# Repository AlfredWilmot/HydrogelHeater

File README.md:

# Overview of temperature controller hardware

[Click to see video showing visualization of system control varialbles during use.](https://drive.google.com/file/d/1k_EgCX9lhL9ZffbRWtTjD1a9hdL3mkuH/view?usp=sharing)

# Use of temperature controller for stimuli-responsive hydrogel research

| Experimental set-up | Close-up of activated temperature-sensitive hydrogel (20x speed) driven by temperature controller|
---|---
 |

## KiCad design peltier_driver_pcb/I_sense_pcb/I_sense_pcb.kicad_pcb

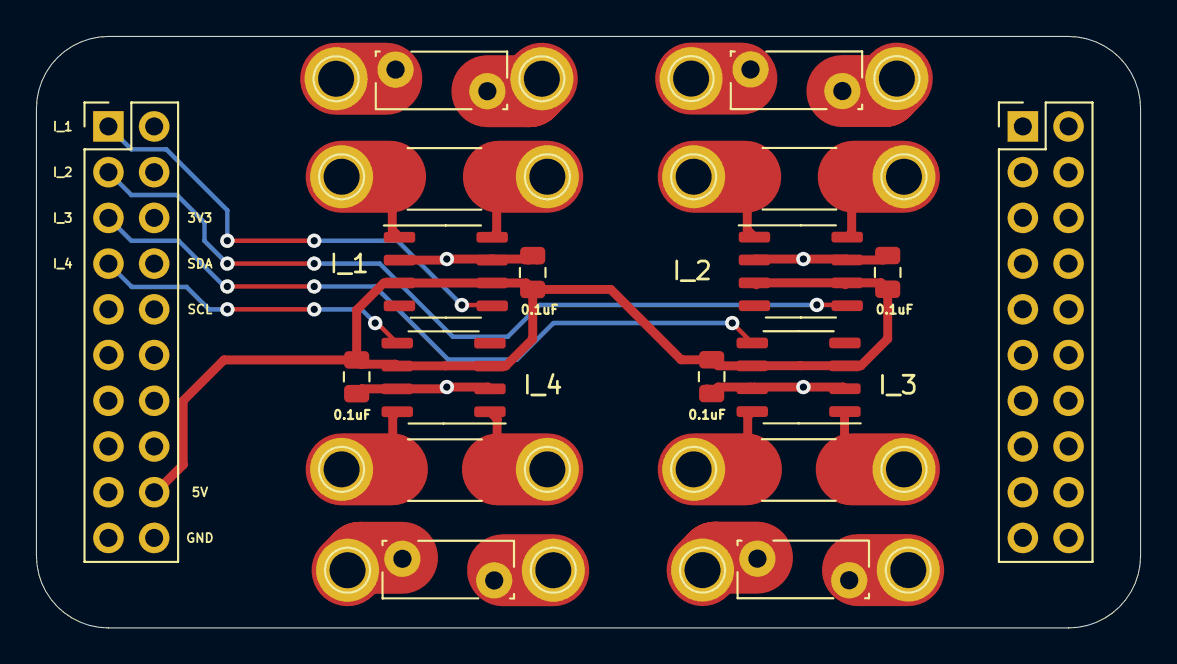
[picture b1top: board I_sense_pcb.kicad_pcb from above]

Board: 2 copper layers, 61.3 x 32.9 mm, 34 parts (0 on the bottom side), 22 nets.

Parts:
C1, C2, C3, C4: 0.1uF; C_0805_2012Metric
F1, F2, F3, F4: 3A hold, 5.1A trip; Fuse_Bourns_MF-RG300
J1, J3, J9, J11: Peltier V-; Pin_D1.0mm_L10.0mm
J2, J4, J10, J12: Driver V-; Pin_D1.0mm_L10.0mm
J5, J6, J13, J14: Peltier V+; Pin_D1.0mm_L10.0mm
J7, J8, J15, J16: Driver V+; Pin_D1.0mm_L10.0mm
J17, J18: Conn_02x10_Top_Bottom; PinHeader_2x10_P2.54mm_Vertical
R1, R2, R3, R4: 0.5m; R_2512_6332Metric
U1, U2, U3, U4: INA283; SO-8_3.9x4.9mm_P1.27mm

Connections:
+5V: C1.2, C2.2, C3.2, C4.2, J17.18, U1.3, U1.6, U2.3, U2.6, U3.3, U3.6, U4.3, U4.6
A0: J17.1, U2.5
A1: J17.3, U3.5
A2: J17.5, U4.5
A3: J17.7, U1.5
GND: C1.1, C2.1, C3.1, C4.1, J17.20, U1.2, U1.7, U2.2, U2.7, U3.2, U3.7, U4.2, U4.7
unnamed: F1.1, J2.1
unnamed: F1.2, J1.1
unnamed: F2.1, J4.1
unnamed: F2.2, J3.1
unnamed: F3.1, J10.1
unnamed: F3.2, J9.1
unnamed: F4.1, J12.1
unnamed: F4.2, J11.1
unnamed: J5.1, R1.2, U1.1
unnamed: J6.1, R2.2, U2.1
unnamed: J7.1, R1.1, U1.8
unnamed: J8.1, R2.1, U2.8
unnamed: J13.1, R3.2, U3.1
unnamed: J14.1, R4.2, U4.1
unnamed: J15.1, R3.1, U3.8
unnamed: J16.1, R4.1, U4.8

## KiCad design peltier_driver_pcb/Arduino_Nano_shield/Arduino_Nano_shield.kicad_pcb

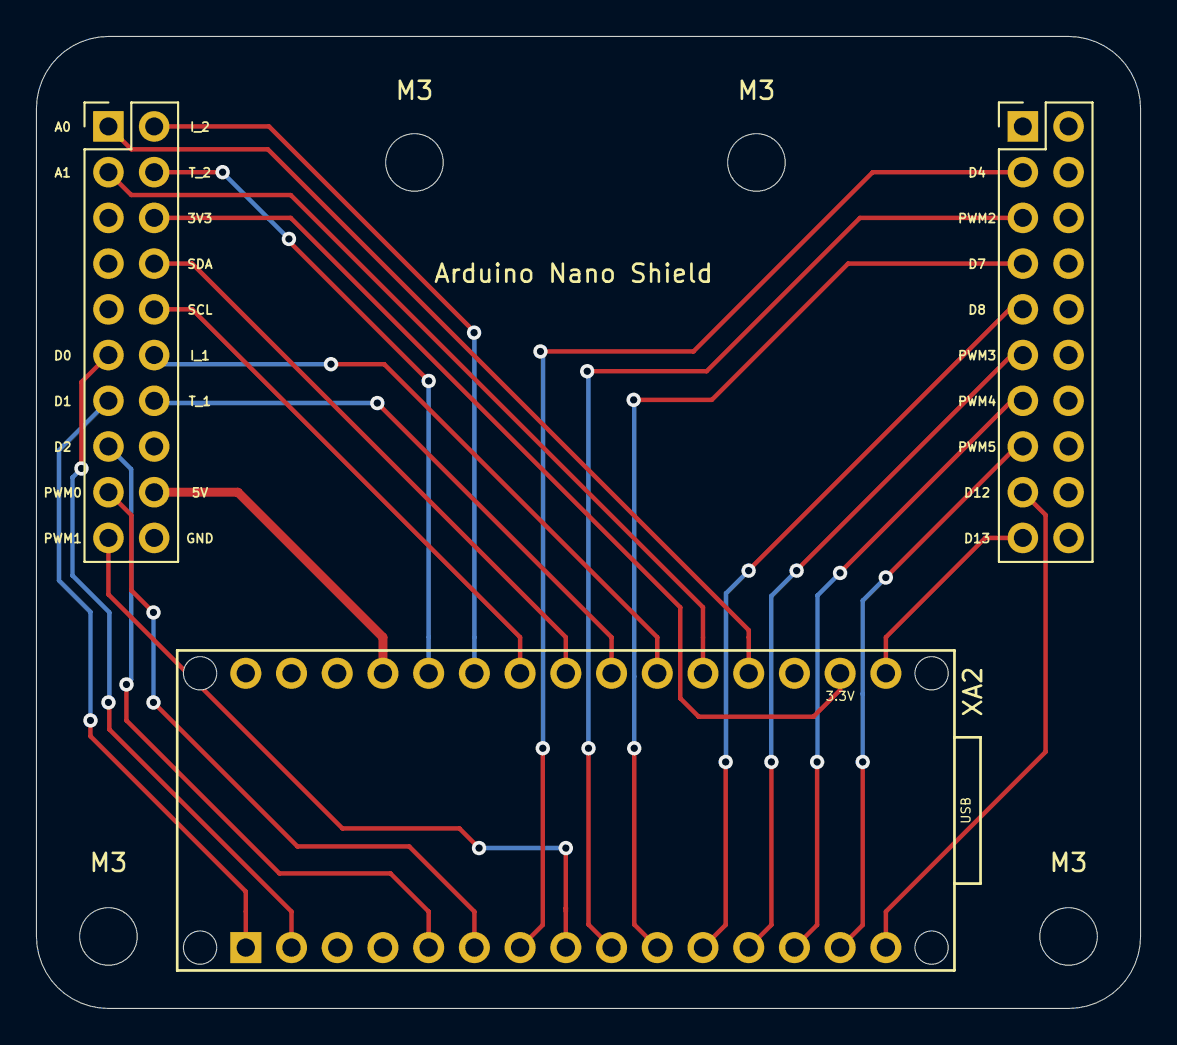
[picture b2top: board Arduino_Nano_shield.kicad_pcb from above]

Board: 2 copper layers, 61.3 x 54.0 mm, 7 parts (0 on the bottom side), 25 nets.

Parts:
H1, H2, H3, H4: MountingHole; MountingHole_3.2mm_M3
J1, J2: Conn_02x10_Top_Bottom; PinHeader_2x10_P2.54mm_Vertical
XA2: Arduino_Nano_Socket

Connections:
+3V3: J1.6, XA2.3V3
+5V: J1.18, XA2.5V
A0: J1.1, XA2.A0
A1: J1.3, XA2.A1
D0: J1.11, XA2.D0
D1: J1.13, XA2.D1
D2: J1.15, XA2.D2
D4: J2.3, XA2.D4
D7: J2.7, XA2.D7
D8: J2.9, XA2.D8
D12: J2.17, XA2.D12
D13: J2.19, XA2.D13
GND: J1.20, XA2.GND1, XA2.GND2
I_sense_1: J1.12, XA2.A2
I_sense_2: J1.2, XA2.A6
PWM0: J1.17, XA2.D3
PWM1: J1.19, XA2.D5
PWM2: J2.5, XA2.D6
PWM3: J2.11, XA2.D9
PWM4: J2.13, XA2.D10
PWM5: J2.15, XA2.D11
SCL: J1.10, XA2.A5
SDA: J1.8, XA2.A4
T_sense1: J1.14, XA2.A3
T_sense2: J1.4, XA2.A7

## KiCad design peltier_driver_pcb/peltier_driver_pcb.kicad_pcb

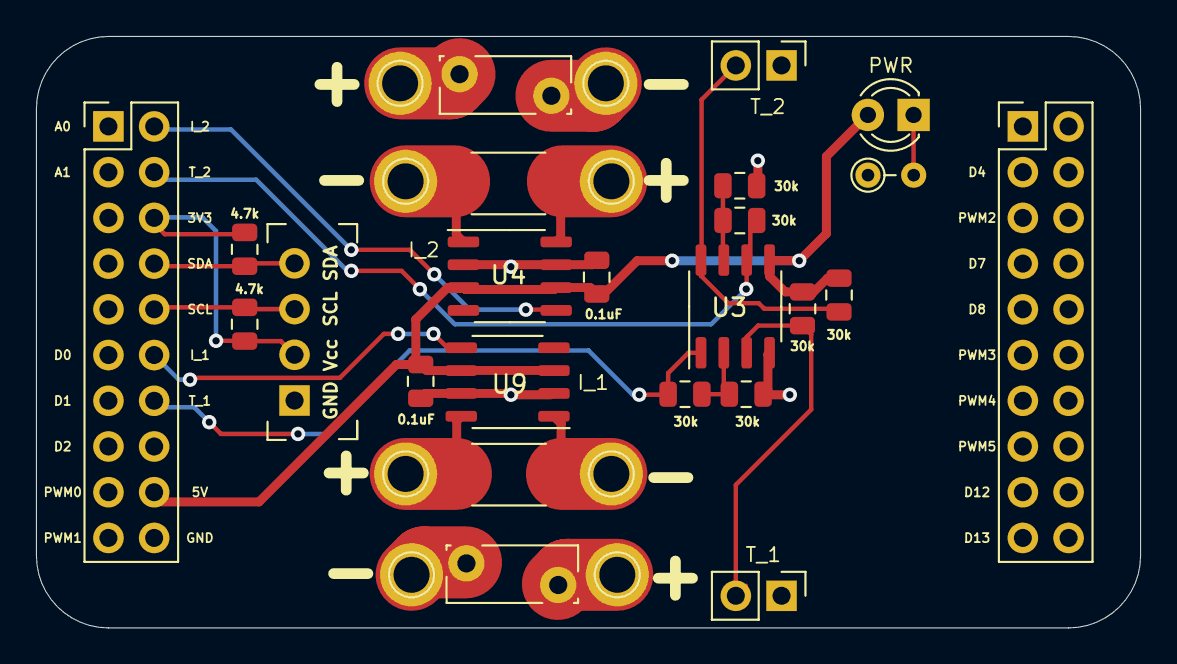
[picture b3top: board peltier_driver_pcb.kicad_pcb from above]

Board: 2 copper layers, 61.3 x 32.9 mm, 32 parts (0 on the bottom side), 22 nets.

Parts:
C1, C6: 0.1uF; C_0805_2012Metric
D1: LED; LED_D3.0mm
F1, F6: 3A hold, 5.1A trip; Fuse_Bourns_MF-RG300
J1, J21: Peltier V-; Pin_D1.0mm_L10.0mm
J2, J22: Driver V-; Pin_D1.0mm_L10.0mm
J3, J10: GA10K4A1_NTC; PinHeader_1x02_P2.54mm_Vertical
J4, J25: Peltier V+; Pin_D1.0mm_L10.0mm
J5, J28: Driver V+; Pin_D1.0mm_L10.0mm
J6, J9: Conn_02x10_Top_Bottom; PinHeader_2x10_P2.54mm_Vertical
R1, R2: 4.7k; R_0805_2012Metric
R3, R4, R5, R7, R8, R9: 30K; R_0805_2012Metric
R6, R14: 0.5m; R_2512_6332Metric
R10: 180; R_Axial_DIN0204_L3.6mm_D1.6mm_P2.54mm_Vertical
U1: OLED_128x32_I2C
U3: MCP602; SO-8_3.9x4.9mm_P1.27mm
U4, U9: INA283; SO-8_3.9x4.9mm_P1.27mm

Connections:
+3V3: J9.6, R1.1, R2.1, U1.2
+5V: C1.2, C6.2, D1.2, J9.18, R3.2, R9.2, U3.5, U4.3, U4.6, U9.3, U9.6
GND: C1.1, C6.1, J3.1, J9.20, J10.1, R5.2, R8.2, R10.1, U1.1, U3.4, U4.2, U4.7, U9.2, U9.7
I_sense_1: J9.12, U9.5
I_sense_2: J9.2, U4.5
unnamed: D1.1, R10.2
unnamed: F1.1, J2.1
unnamed: F1.2, J1.1
unnamed: F6.1, J22.1
unnamed: F6.2, J21.1
unnamed: J3.2, R3.1, U3.3
unnamed: J4.1, R6.2, U4.1
unnamed: J5.1, R6.1, U4.8
unnamed: J10.2, R9.1, U3.8
unnamed: J25.1, R14.2, U9.1
unnamed: J28.1, R14.1, U9.8
unnamed: R4.2, R5.1, U3.2
unnamed: R7.2, R8.1, U3.7
SCL: J9.10, R1.2, U1.3
SDA: J9.8, R2.2, U1.4
T_sense1: J9.14, R4.1, U3.1
T_sense2: J9.4, R7.1, U3.6

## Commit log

2020-05-29 Changed to 16x02 LCD
2020-05-29 Initial PCB files
2020-05-29 added I-sense IC and 128x32 OLED footprint
2020-05-29 added cad files to user-made PCB footprints
2020-05-29 house-keeping
2020-05-29 properly saved 3D models to footprint files
2020-05-30 updating PCB
2020-05-31 added TI RTD guide
2020-05-31 single Pt1000, wheatstone bridge diff amplifier
2020-06-01 some tweaks
2020-06-02 I-source for Pt1000, fixed I2C level mismatch, added mounting holes
2020-06-03 resettable fuse, rearranged board for neatness
2020-06-03 added break-out for remaining Arduino pins
2020-06-06 some scripting to calculate values for NTC circuit and conversion
2020-06-07 comparing look-up table vals to Beta-model vals
2020-06-07 NTC selection guide note
2020-06-07 Exploring thermistor error calculations
2020-06-07 starting to implement requested changes
2020-06-08 got some sexy LTspice sims boiii
2020-06-08 house keeping
2020-06-10 ltspice sims and modular pcb v1
2020-06-10 v1 PCB ready for show
2020-06-15 testing INA283 in LTspice
2020-06-16 updating gerber files for UI PCB
2020-06-16 better arduino ftprnt lib, first iteration of shield PCBs
2020-06-17 matching PCB dimensions to each other
2020-06-17 final touches for second design iteration
2020-07-03 initializing workspace for my home coil system
2020-07-05 Added links to useful analog theory application notes
2020-07-18 experimental complimentary pwm-driven VCCS
2020-07-18 measure voltage from T-sense and display via serial, need to convert to temp
2020-07-18 added OLED 128x32 adafruit lib, displaying data onto display
2020-07-18 adjusting font size
2020-07-19 display of uncalibrated temperature; most accurate between [25C, 100C]
2020-10-26 Porting work to VS code, basic demo finished
2020-11-07 properly migrating pio project... I think
2020-11-07 implemented overhead IR-sensor
2020-11-29 starting to implement PID loop and therocouple
2020-11-29 fixed multiple declaration issue with PID stuff
2020-12-07 using digital clk to read thermocouple, MX6675 has 250ms conversion time!
2020-12-07 added some references
2020-12-13 crude non-blocking timer for non-blocking sampling of thermocouple
2020-12-14 encoder more or less functions
2020-12-14 slightly unstable when encoder is spammed, but functional
2020-12-14 Arduino delays + ISRs = deadlock, don't mix these two
2020-12-14 encoder behaves and can toggle between two temp sensors using btn press
2020-12-14 basic PID temperature control-- needs to adapt to bleeding effects
2020-12-15 deserializing arduino output to plot/ inspect data
2020-12-15 plotting Ardunio serial data using python
2020-12-15 plotting both set-point and measured temperature
2021-01-03 Tweaking PID gains, and setting soft limit
2021-01-03 set-point resolution is now 0.1C
2021-01-03 slightly better err handling, but still need to unplug/ replug usb cable after closing port in software
2021-01-03 attempting to improve control loop
2021-01-04 cumulative error controller seems to hold a position with high precision but takes a while to reach the SP
2021-01-04 good result my G
2021-01-04 sending driving_signal data over serial
2021-01-04 presenting close-up of plots
2021-01-04 need to address aggresive rate of change when nearing SP
2021-01-04 improved analytics, need to add time-tracking features
2021-01-05 making realtime analytics more interesting
2021-01-05 ~fixed tol band tracking issue
2021-01-05 fixed it properly (but lazily imo)
2021-01-05 implemented my own PID controller
2021-01-05 blah
2021-01-06 added settling latency & oscillator counter to analytics plot
2021-01-06 nice rolling average over n-samples
2021-01-06 cleaning graphs
2021-01-06 Mostly done with plotting, only some tweaks here/there left
2021-01-06 some visualization improvements and a cheeky pic
2021-06-10 minor label change
2021-06-10 something to do with PID loop
2021-06-10 implemented second cascaded peltier element
2021-09-28 overview image of temperature controller hardware
2021-09-29 Keeping it short and sweet
